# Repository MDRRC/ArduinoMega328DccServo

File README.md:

# ArduinoMega328DccServo

A(nother) Arduino based DCC decoder for 8 servo's. Servo address and positions can be changed using CV's or by a terminal program.
It uses an Atmel Mega328P processor running at 16MHz. 
The processor itself must be programmed with a Arduino bootloader and the fuses must be set to external xtal.

The decoder uses the [NMRA DCC Library](https://www.arduino.cc/reference/en/libraries/nmradcc/) and the design is based on the examples.
Adress range is limited to 255.  

## Programming
 * Make sure the Atmel processor has the Arduino bootloader in it.
 * Connect a USB serial to TTL converter to X1.
 * Press the reset button and keep it pressed.
 * Press upload in the IDE.
 * Release the reset button.
 * Hex file is uploaded.
 * Change CV's according the CV numbers defined in FactoryDefaultCVs[] 
 
At first time power on the default CV values are set. The led flashes fast, after CV's are written a reset will be performed. 
When writing CV value 8 all CV values are written to there default values.  

## Connecting 
 * Supply voltage 9V to X2.
 * DCC signal to X20.
 * Servo's to Sv1 .. SV7 (servo connection is signal, supply voltage, ground).

## Simple console
To list or chamge CV values 
 * Connect a serial terminal and set baudrate to 57600
 * Pull pin 7 (CONS in schematic)m to ground using jumper JP1
 * To change a CV value enter S xx yy <ENTER> where xx the CV nummer is and yy the value.

 * If the entered command is not ok message CV command entry not ok!! will appear.

 * To list the CV values press L <ENTER> 

 * Press H <ENTER> for minimal help screen.

## CV programming (programming track)
 * Connect the decoder to a programming track.
 * Enter CV number and CV value.
 * The servo will move to the new minimal or maximum positions when changed. 

## POM programming 
Test only with [MDRRC-II](https://robertdotevers.wordpress.com/134-2/) Menu TO -> POM when MDRRC-II is on.
 * Connect the decoder to the main track (no need for programming track). 
   * Enter the address of the servo to be changed. 
   * Enter CV number 1 to change the address.
   * Enter CV Number 2 to change the minimum angle of the servo
   * Enter CV number 3 to change the maximum angle of the servo.
 * Enter the value 

Yes, you do not need to enter the CV values as shown in an image above. Just 1, 2, or 3.
 
## License
NONE! Feel free to use / change the source code, schematic and PCB data.
PCB's are NOT sold, so if you want a PCB just order the PCB's yourself. 
If you use this decoder it's on OWN risk!!!

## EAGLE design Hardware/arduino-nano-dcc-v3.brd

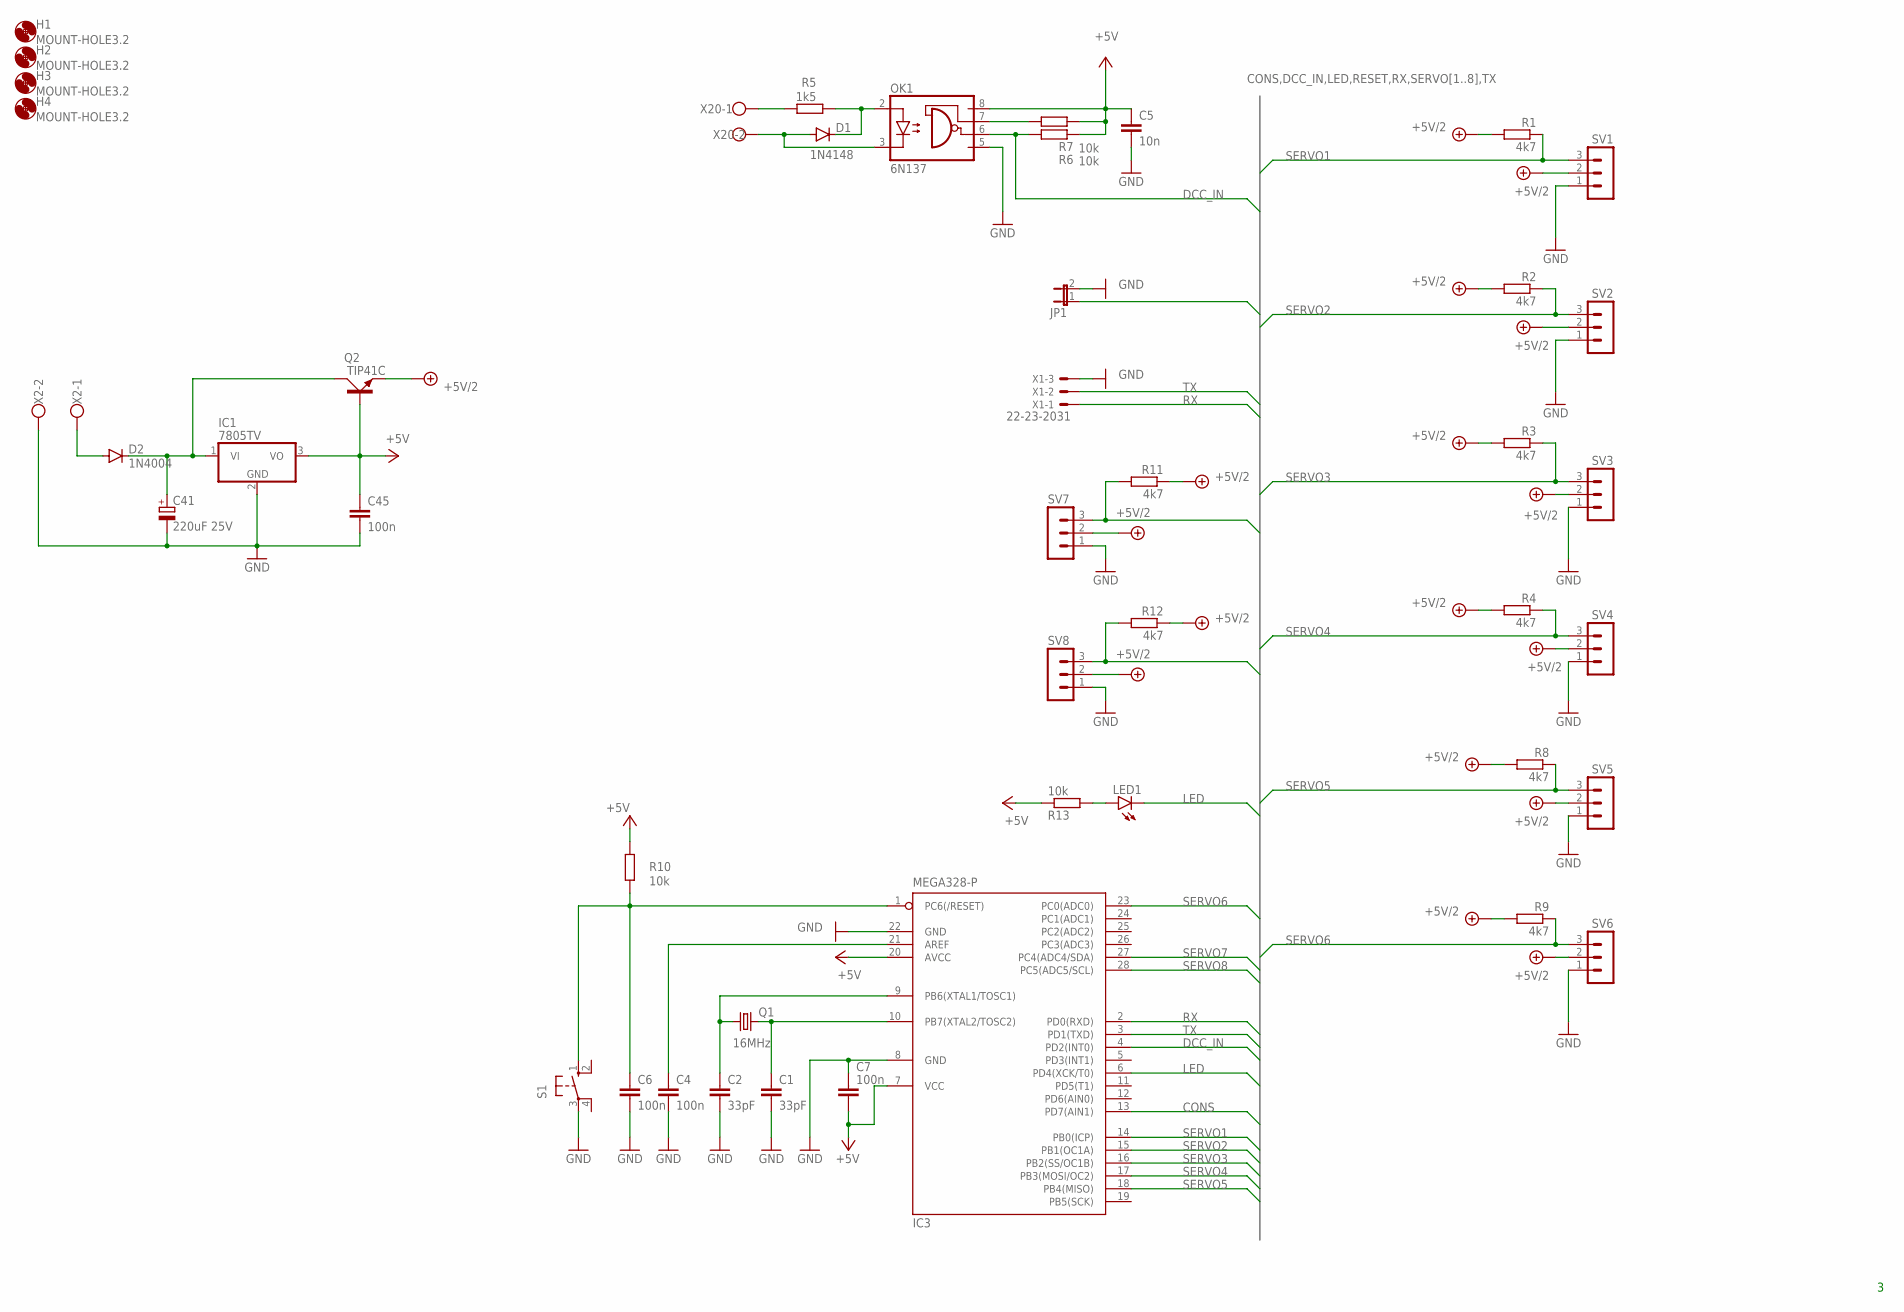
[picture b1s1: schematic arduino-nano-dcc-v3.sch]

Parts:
C1, C2: 33pF; C025-024X044
C4, C6, C7, C45: 100n; C050-024X044
C5: 10n; C050-024X044
C41: 220uF 25V; E5-8,5
D1: 1N4148; DO35-7
D2: 1N4004; DO41-10
H1, H2, H3, H4: MOUNT-HOLE3.2; 3,2
IC1: 7805TV; TO220V
IC3: MEGA328-P; DIL28-3
JP1: JP1E; JP1
LED1: LED3MM
OK1: 6N137; DIL08
Q1: 16MHz; HC49U-V
Q2: TIP41C; TO220AV
R1, R2, R3, R4, R8, R9, R11: 4k7; 0204/7
R5: 1k5; 0204/7
R6, R7, R10: 10k; 0204/7
R12: 4k7; 0204/5
R13: 10k; 0204V
S1: 10-XX; B3F-10XX
SV1, SV2, SV3, SV4, SV5, SV6, SV7, SV8: MA03-1
X1: 22-23-2031
X2, X20: W237-102

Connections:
+5V: C5.1, C7.2, C45.1, IC1.3 (VO), IC3.7 (VCC), IC3.20 (AVCC), OK1.8 (VCC), Q2.B, R6.1, R7.1, R10.1, R13.1
+5V/2: Q2.E, R1.2, R2.2, R3.2, R4.2, R8.2, R9.2, R11.1, R12.1, SV1.2, SV2.2, SV3.2, SV4.2, SV5.2, SV6.2, SV7.2, SV8.2
CONS: IC3.13 (PD7(AIN1)), JP1.1
DCC_IN: IC3.4 (PD2(INT0)), OK1.6 (VO), R7.2
GND: C1.2, C2.2, C4.2, C5.2, C6.2, C7.1, C41.-, C45.2, IC1.2 (GND), IC3.8 (GND), IC3.22 (GND), JP1.2, OK1.5 (GND), S1.3, SV1.1, SV2.1, SV3.1, SV4.1, SV5.1, SV6.1, SV7.1, SV8.1, X1.3, X2.2
LED: IC3.6 (PD4(XCK/T0)), LED1.K (C)
unnamed: C41.+, D2.C, IC1.1 (VI), Q2.C
unnamed: D2.A, X2.1
unnamed: C2.1, IC3.9 (PB6(XTAL1/TOSC1)), Q1.1
unnamed: C1.1, IC3.10 (PB7(XTAL2/TOSC2)), Q1.2
unnamed: C6.1, IC3.1 (PC6(/RESET)), R10.2, S1.1 (S)
unnamed: C4.1, IC3.21 (AREF)
unnamed: LED1.A, R13.2
unnamed: D1.C, OK1.2 (A), R5.1
unnamed: OK1.7 (VE), R6.2
unnamed: D1.A, OK1.3 (C), X20.2
unnamed: R5.2, X20.1
RX: IC3.2 (PD0(RXD)), X1.1
SERVO1: IC3.14 (PB0(ICP)), R1.1, SV1.3
SERVO2: IC3.15 (PB1(OC1A)), R2.1, SV2.3
SERVO3: IC3.16 (PB2(SS/OC1B)), R3.1, SV3.3
SERVO4: IC3.17 (PB3(MOSI/OC2)), R4.1, SV4.3
SERVO5: IC3.18 (PB4(MISO)), R8.1, SV5.3
SERVO6: IC3.23 (PC0(ADC0)), R9.1, SV6.3
SERVO7: IC3.27 (PC4(ADC4/SDA)), R11.2, SV7.3
SERVO8: IC3.28 (PC5(ADC5/SCL)), R12.2, SV8.3
TX: IC3.3 (PD1(TXD)), X1.2

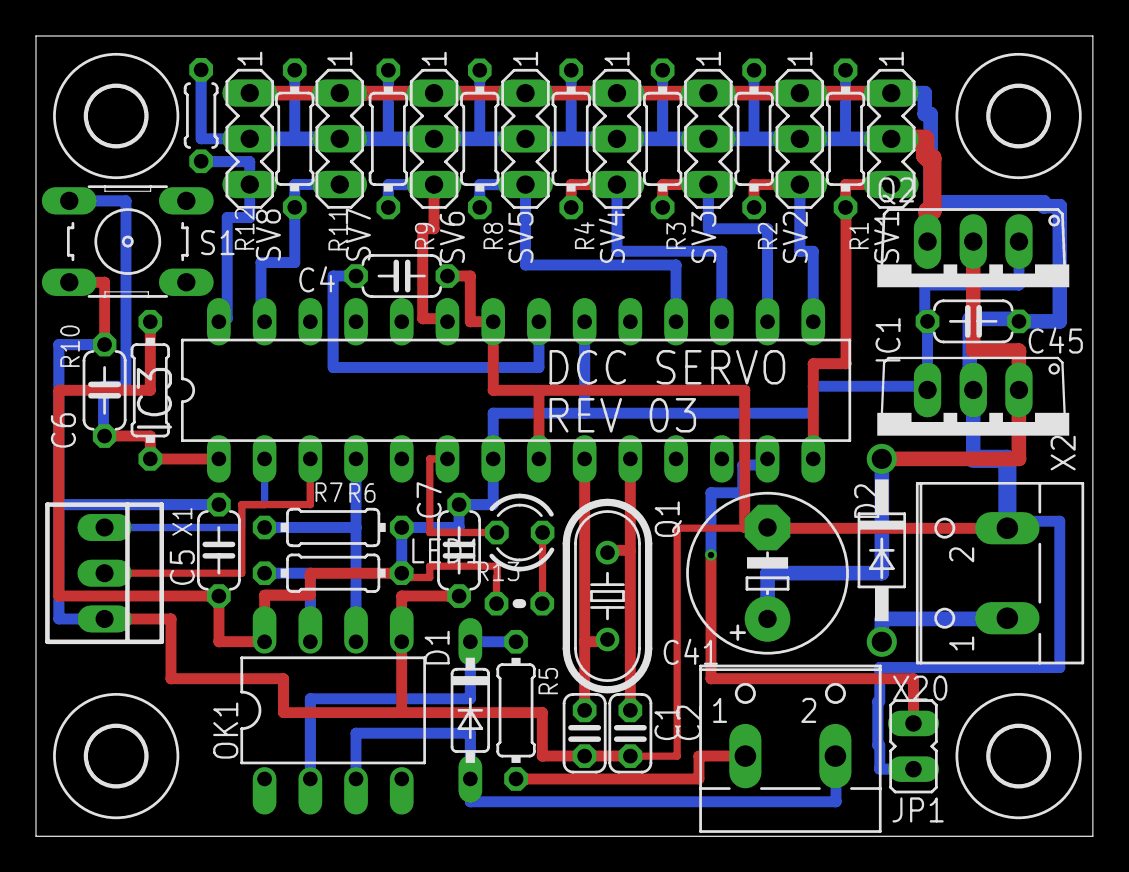
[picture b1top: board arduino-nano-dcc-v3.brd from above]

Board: 2 copper layers, 58.7 x 44.5 mm, 46 parts (0 on the bottom side), 27 nets.

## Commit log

2022-03-20 Added files.
2022-03-20 Arduino want's sorce code in a dir..
2022-03-20 Changes * Added TIP for 5V supply servo's, * Initial routing.
2022-03-21 Changes : * Last traces routed. * Extended to 8 servo's * PCB somewhat bigger so 8 servo connections fit between the mounting holes.
2022-03-22 Added led and added zipfile for pcb production at JclPcb.
2022-04-16 8 PWM channels now for PCB.
2022-04-16 Indent by Arduino IDE.
2022-04-17 * Pin PB5 does not work, so moved to PC0. * Run led added.
2022-04-17 Deleted file.
2022-04-17 Added code for Slober environment.
2022-04-17 clang off/on so table is readable...
2022-04-17 Renamed directory.
2022-04-18 Use of nrma dcc library. Servo settings are now in CV's. Servo pin number also, just to avoid a double table with pin numbers..
2022-04-20 Adding some debug for checking setting servo's.
2022-04-20 * Added cyclic read of CV's. When changed set new min/max value and activate servo to new position. * Added comments headers.
2022-04-20 Sloeber / Eclipse stuff.
2022-04-20 When CV reset perform a reset of the processor. Also blink the led with delay indicating reset is ongoing.
2022-04-20 Deleted file, generated each time.
2022-04-20 Comment updated.
2022-04-20 Renamed off/on to min/max.
2022-04-20 Commments updated.
2022-04-21 Set max values to lower value for batter match with servo's on my railroad.
2022-04-21 Updated zip file and added pdf with components.
2022-04-21 Added values to components and added partlist.
2022-04-23 Added image.
2022-04-23 Updating file.
2022-04-23 Updated text.
2022-04-23 Typo.
2022-04-23 Text corrections.
2022-04-23 Text update.
2022-05-26 If pin 7 is connected to ground the serial port can be used to list and set CV'values using for example Putty or Realterm.
2022-05-26 Call Dcc.process more often.
2022-05-26 Updated hardware t V3, added to pin D7 jumper to enable console mode.
2022-05-27 Showing DCC values updated.
2022-05-27 Added some text on listing and setting CV values.
2022-05-27 Help and failed CV command added.
2022-11-27 Connections to X2 and X20 where mixed up, corrected.
2022-12-04 Max addresses mentioned.
2022-12-04 Working commit for implementing POM (Programming On Main) for the servo decoder.
2022-12-05 Debug removed.
2022-12-06 Adding text for POM programming.
2022-12-06 Updated POM and added CV programming.
